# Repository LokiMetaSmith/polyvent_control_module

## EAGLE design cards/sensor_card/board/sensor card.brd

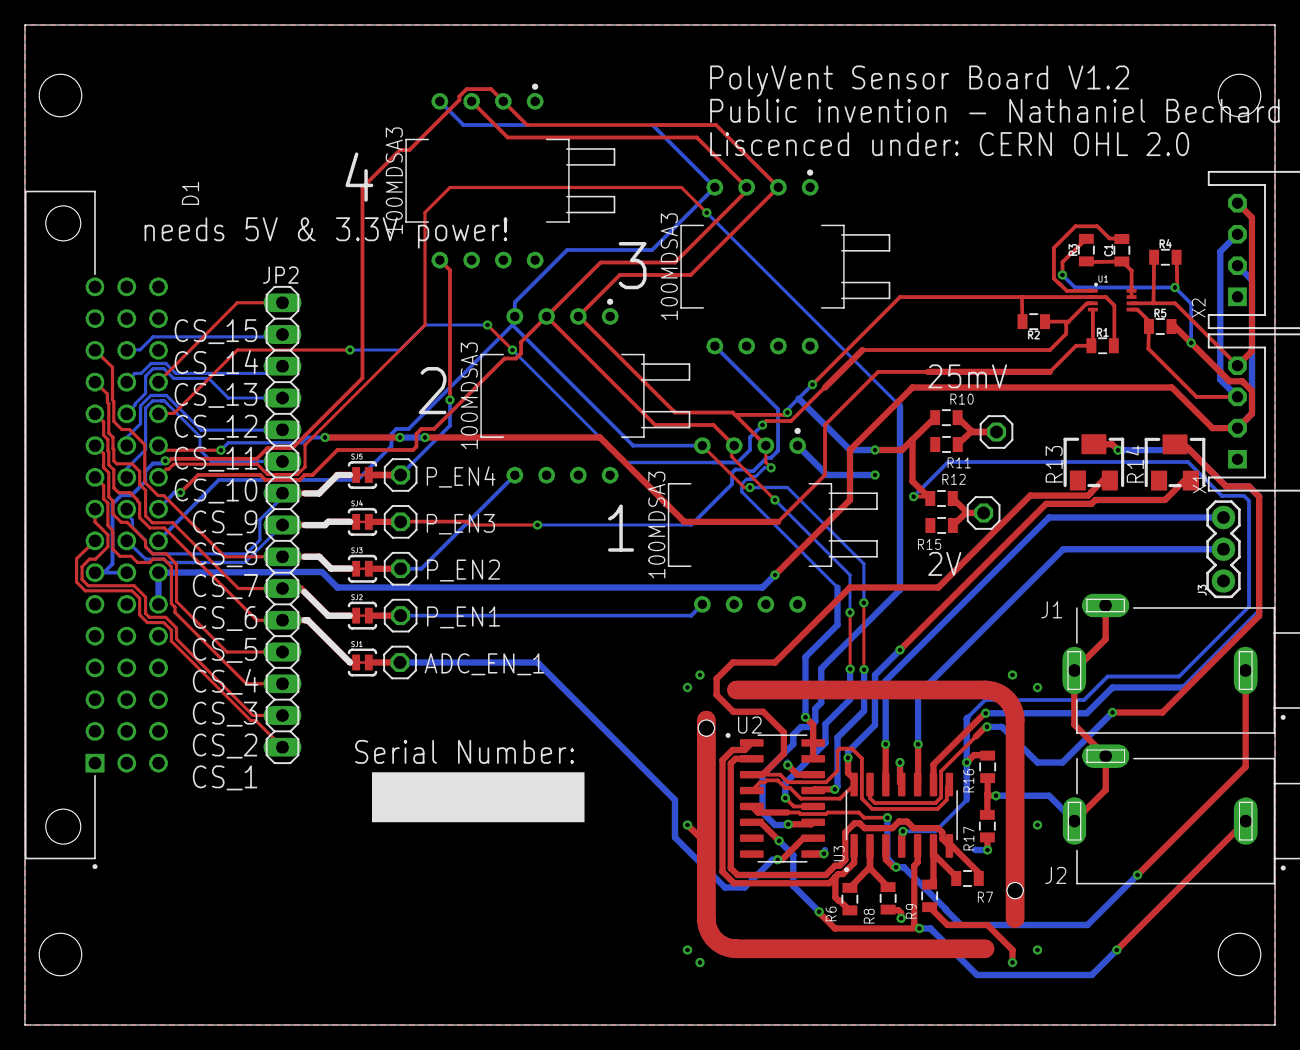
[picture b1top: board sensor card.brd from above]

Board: 2 copper layers, 100.0 x 80.0 mm, 45 parts (0 on the bottom side), 46 nets.

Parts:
C1: 100pF; 0805
D1: 09231486921; HARTING_09231486921
J1, J2: MJ-3536N; CUI_MJ-3536N
J3: 1X03
JP2: 1X15
P1, P2, P3, P4, P5, P6, P7: 1X01
R1, R2, R4, R5: 2.2k; 0805
R3: 200K; 0805
R6, R7: 30k, 0.1%, 25ppm/C; 0805
R8, R9: 1k, 0.1%, 25ppm/C; 0805
R10: 132k, 1%; 0805
R11: 1k, 1%; 0805
R12: 6.5k, 1%; 0805
R13, R14: RTRIM3214W
R15: 10k, 1%; 0805
R16: 16.5k, 1%; 0805
R17: 100, 1%; 0805
SJ1, SJ2, SJ3, SJ4, SJ5: SOLDERJUMPERTRACE; SJ_2S-TRACE
U1: PCA9306; VSSOP_8PIN
U2: MCP3008-I/SL; SOIC127P600X175-16N
U3: MCP6064-E/SL; SOIC127P600X175-14N
U$1, U$3, U$4, U$5: SCCDRRV100MDSA3SSCDRRV100MDSA3; DIP1270W53P254L1303H508Q8B
U$2: EMI_SHIELD; 3671250
X1, X2: S4B-XH-A

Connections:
2V: P7.1, R12.1, R15.2
3.3V: D1.7, D1.23, R1.2, R2.2, R10.2, R12.2, R16.2, U1.P2, U2.15, U2.16, U3.4, U$1.VSUPPLY, U$3.VSUPPLY, U$4.VSUPPLY, U$5.VSUPPLY
5V: D1.38, D1.39, R3.2, R4.2, R5.2, X1.2, X2.2
50MILIVOLT: P1.1, R10.1, R11.2
AMP_ADC_1: J3.2, U3.10
AMP_ADC_2: J3.3, U3.12
CH0: R6.1, U2.1, U3.1
CH1: R7.1, U2.2, U3.7
CH2: R13.3, U2.3, U3.8
CH3: R14.3, U2.4, U3.14
CS_1: D1.8, JP2.15
CS_2: D1.9, JP2.14
CS_3: D1.10, JP2.13
CS_4: D1.11, JP2.12
CS_5: D1.12, JP2.11, SJ1.1
CS_6: D1.13, JP2.10, SJ2.1
CS_7: D1.14, JP2.9, SJ3.1
CS_8: D1.24, JP2.8, SJ4.1
CS_9: D1.25, JP2.7, SJ5.1
CS_10: D1.26, JP2.6
CS_11: D1.27, JP2.5
CS_12: D1.28, JP2.4
CS_13: D1.29, JP2.3
CS_14: D1.30, JP2.2
CS_15: D1.45, JP2.1
GND: C1.2, D1.1, D1.2, D1.3, D1.4, D1.17, D1.18, D1.19, D1.33, D1.34, D1.35, J3.1, R8.1, R9.1, R11.1, R13.1, R14.1, R15.1, R17.1, U1.P1, U2.9, U2.14, U3.11, U$1.GND, U$2.P$1, U$3.GND, U$4.GND, U$5.GND, X1.1, X2.1
MISO: D1.41, U2.12, U$1.MISO, U$3.MISO, U$4.MISO, U$5.MISO
MOSI: D1.42, U2.11
unnamed: R14.2, U3.13
unnamed: P6.1, SJ1.2, U2.10
unnamed: P2.1, SJ2.2, U$5.SS
unnamed: R13.2, U3.9
unnamed: R6.2, R8.2, U3.2
unnamed: R7.2, R9.2, U3.6
unnamed: P4.1, SJ4.2, U$3.SS
unnamed: P5.1, SJ5.2, U$1.SS
unnamed: J1.2, J1.3, J2.2, J2.3, R16.1, R17.2
unnamed: P3.1, SJ3.2, U$4.SS
OXYGEN1: J1.1, U2.5, U3.3
OXYGEN2: J2.1, U2.6, U3.5
SCK: D1.40, U2.13, U$1.SCLK, U$3.SCLK, U$4.SCLK, U$5.SCLK
SCL: D1.44, R2.1, U1.P3
SCL_SV: R4.1, U1.P6, X1.4, X2.4
SDA: D1.43, R1.1, U1.P4
SDA_5V: R5.1, U1.P5, X1.3, X2.3
VREF2_IN: C1.1, R3.1, U1.P7, U1.P8

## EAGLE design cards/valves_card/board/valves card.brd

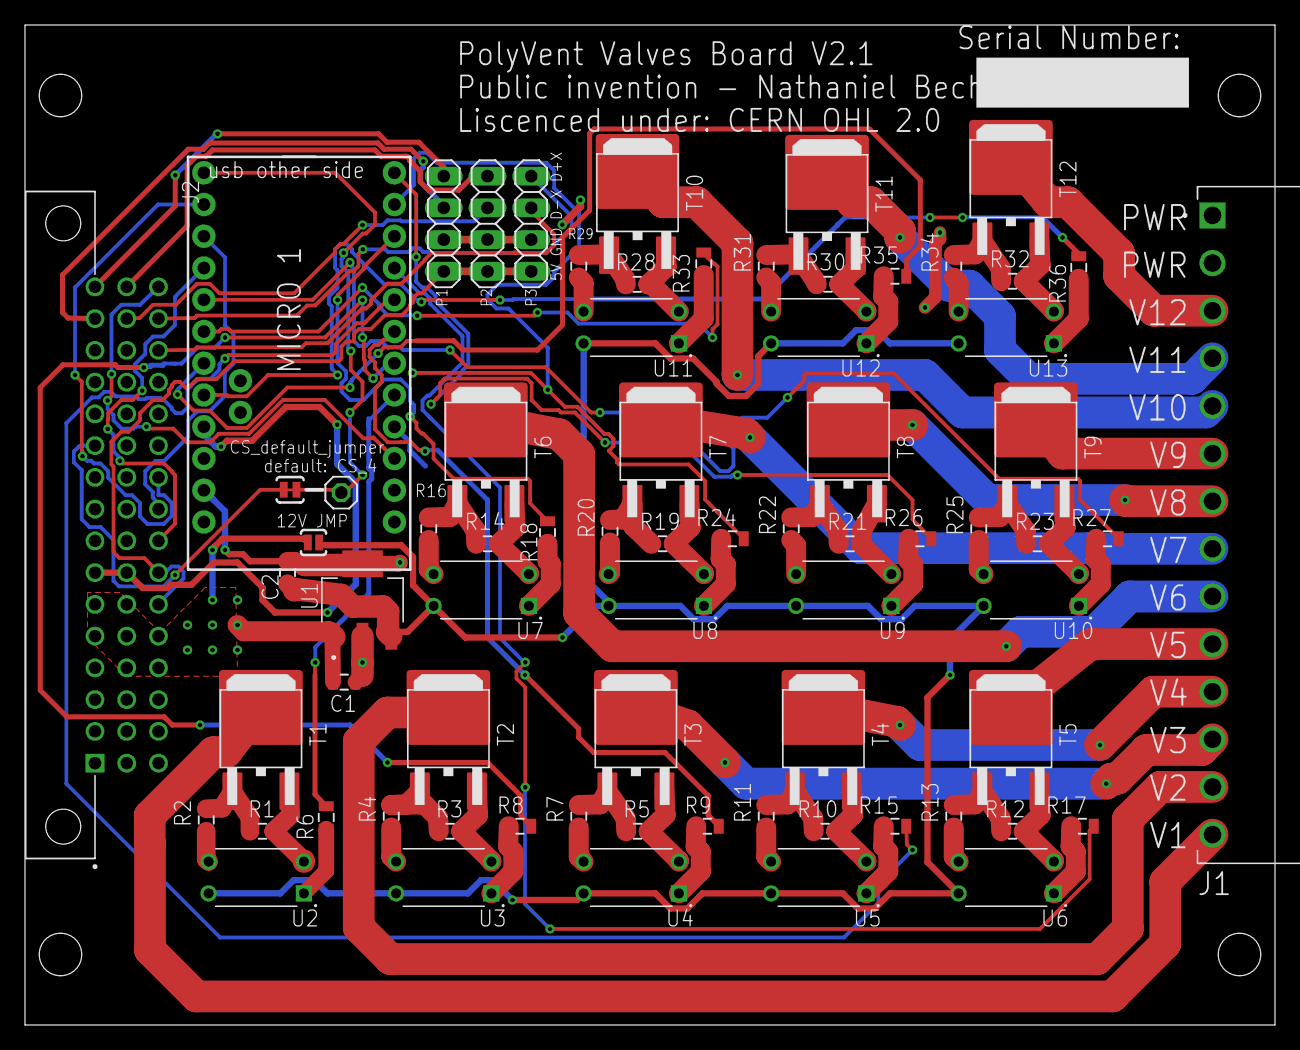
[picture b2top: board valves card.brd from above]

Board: 2 copper layers, 100.0 x 80.0 mm, 72 parts (0 on the bottom side), 77 nets.

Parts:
12V_VALVES_JUMPER: SJ_2S-NO
C1: 0.1Uf, 50V; 0805
C2: 10Uf, 50V; 0805
J1: TBP02R1-381-14BE; CUI_TBP02R1-381-14BE
J2: 09231486921; HARTING_09231486921
JP1: 1X01
JP2, JP3, JP4: 1X04
M2: SAM_D21_MINI_BREAKOUT; JP1_SPARKFUN-SAMD21-MINI-BREAKOUT-V10
R1, R3, R5, R10, R12, R14, R19, R21, R23, R28, R30, R32: 10k; 0805
R2, R4, R7, R11, R13, R16, R20, R22, R25, R29, R31, R34: 600; 0805
R6, R8, R9, R15, R17, R18, R24, R26, R27, R33, R35, R36: 100; 0805
SJ1: SOLDERJUMPERTRACE; SJ_2S-TRACE
T1, T2, T3, T4, T5, T6, T7, T8, T9, T10, T11, T12: IRLZ44NSTRLPBF; DPAK_TO252
U1: LM2937IMP-12; SOT230P700X180-4N
U2, U3, U4, U5, U6, U7, U8, U9, U10, U11, U12, U13: EL817(D)-ND; DIP4

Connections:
3.3V: J2.7, J2.23, M2.4@JP2
5V: J2.38, J2.39, JP2.1, JP3.1, JP4.1
12V: 12V_VALVES_JUMPER.2, C2.1, U1.3, U2.4, U3.4, U4.4, U5.4, U6.4, U7.4, U8.4, U9.4, U10.4, U11.4, U12.4, U13.4
24V/12V: 12V_VALVES_JUMPER.1, C1.1, J1.1, J1.2, J2.5, J2.6, J2.20, J2.21, J2.22, J2.36, J2.37, U1.1
CS_4: J2.11, SJ1.2
DRAIN1: J1.14, T1.2
DRAIN2: J1.13, T2.2
DRAIN3: J1.12, T3.2
DRAIN4: J1.11, T4.2
DRAIN5: J1.10, T5.2
DRAIN6: J1.9, T6.2
DRAIN7: J1.8, T7.2
DRAIN8: J1.7, T8.2
DRAIN9: J1.6, T9.2
DRAIN10: J1.5, T10.2
DRAIN11: J1.4, T11.2
DRAIN12: J1.3, T12.2
GND: C1.2, C2.2, J2.1, J2.2, J2.3, J2.4, J2.17, J2.18, J2.19, J2.33, J2.34, J2.35, JP2.2, JP3.2, JP4.2, M2.2@JP2, M2.9@JP1, R1.1, R3.1, R5.1, R10.1, R12.1, R14.1, R19.1, R21.1, R23.1, R28.1, R30.1, R32.1, T1.3, T2.3, T3.3, T4.3, T5.3, T6.3, T7.3, T8.3, T9.3, T10.3, T11.3, T12.3, U1.2, U1.4, U2.2, U3.2, U4.2, U5.2, U6.2, U7.2, U8.2, U9.2, U10.2, U11.2, U12.2, U13.2
MISO: J2.41, M2.10@JP2
MOSI: J2.42, M2.11@JP2
unnamed: JP1.1, M2.12@JP2, SJ1.1
unnamed: R6.2, U2.1
unnamed: R1.2, R2.2, T1.1
unnamed: R2.1, U2.3
unnamed: R3.2, R4.2, T2.1
unnamed: R4.1, U3.3
unnamed: R8.2, U3.1
unnamed: R5.2, R7.2, T3.1
unnamed: R7.1, U4.3
unnamed: R9.2, U4.1
unnamed: R10.2, R11.2, T4.1
unnamed: R11.1, U5.3
unnamed: R15.2, U5.1
unnamed: R12.2, R13.2, T5.1
unnamed: R13.1, U6.3
unnamed: R17.2, U6.1
unnamed: R14.2, R16.2, T6.1
unnamed: R16.1, U7.3
unnamed: R18.2, U7.1
unnamed: R19.2, R20.2, T7.1
unnamed: R20.1, U8.3
unnamed: R24.2, U8.1
unnamed: R21.2, R22.2, T8.1
unnamed: R22.1, U9.3
unnamed: R26.2, U9.1
unnamed: R23.2, R25.2, T9.1
unnamed: R25.1, U10.3
unnamed: R27.2, U10.1
unnamed: R28.2, R29.2, T10.1
unnamed: R29.1, U11.3
unnamed: R33.2, U11.1
unnamed: R30.2, R31.2, T11.1
unnamed: R31.1, U12.3
unnamed: R35.2, U12.1
unnamed: R32.2, R34.2, T12.1
unnamed: R34.1, U13.3
unnamed: R36.2, U13.1
RESET: J2.48, M2.10@JP1
SCK: J2.40, M2.9@JP2
SOL1: M2.8@JP1, R6.1
SOL2: M2.7@JP1, R8.1
SOL3: M2.6@JP1, R9.1
SOL4: M2.5@JP1, R15.1
SOL5: M2.4@JP1, R17.1
SOL6: M2.3@JP1, R18.1
SOL7: M2.2@JP1, R24.1
SOL8: M2.1@JP1, R26.1
SOL9: M2.8@JP2, R27.1
SOL10: M2.7@JP2, R33.1
SOL11: M2.6@JP2, R35.1
SOL12: M2.5@JP2, R36.1
USB1_D+: J2.16, JP2.4
USB1_D-: J2.15, JP2.3
USB2_D+: J2.32, JP3.4
USB2_D-: J2.31, JP3.3
USB3_D+: J2.47, JP4.4
USB3_D-: J2.46, JP4.3

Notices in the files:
cards/sensor_card/board/sensor card.brd:
Liscenced under: CERN OHL 2.0
parts and their libraries:
SparkFun-Passives: Licensing: CC v3.0 Share-Alike You are welcome to use this library for commercial purposes.
SparkFun-IC-Comms: Licensing: Creative Commons ShareAlike 4.0 International - https://creativecommons.org/licenses/by-sa/4.0
